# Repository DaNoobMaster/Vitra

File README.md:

# Vitra – AI Waste Classification System

Computer vision based trash can sorting system that runs on a raspberry-pi with a custom 3d printed model. Involves both a local model and 3 cloud based AI models for judgement. This creates a layer on top of all of the cloud models to merge results and increase accuracy. This project is intended to promote proper waste segregation and improve recycling opportunities. Using this in households can be a step in the right direction towards sustainability, a growing problem in our current society.

Waste is classified into 3 categories : 
- **Wet:** Food waste, banana peels, leftovers, and organic scraps.
- **Plastic:** Plastic bottles, containers, wrappers, and packaging.
- **Metal:** Metal cans, aluminium foil, and other metallic waste.

Prototype without PCB

BUILD INSTRUCTIONS-

-Corresponding Support arms are to be screwed into the male and female parts using M4 screws
-The male and female bin parts contain a dovetail slot in order to allow them to slide and lock with one another. Slide the male part into its female counterpart forming 1 large cylinderical bin.
-The Divider can be slided in between the cylinder.
-The Nema 17 Motor is to be mounted on the top disk
-The raspberry pi and servo are to be mounted on the arm
-the arm also contains dovetail joints to connect the camera holder to it while allowing it to print with ease.
-The raspberry pi camera is to be slid into the camera slot of the arm
-The arm is to be attached to a NEMA 17 coupler then attached to the nema 17

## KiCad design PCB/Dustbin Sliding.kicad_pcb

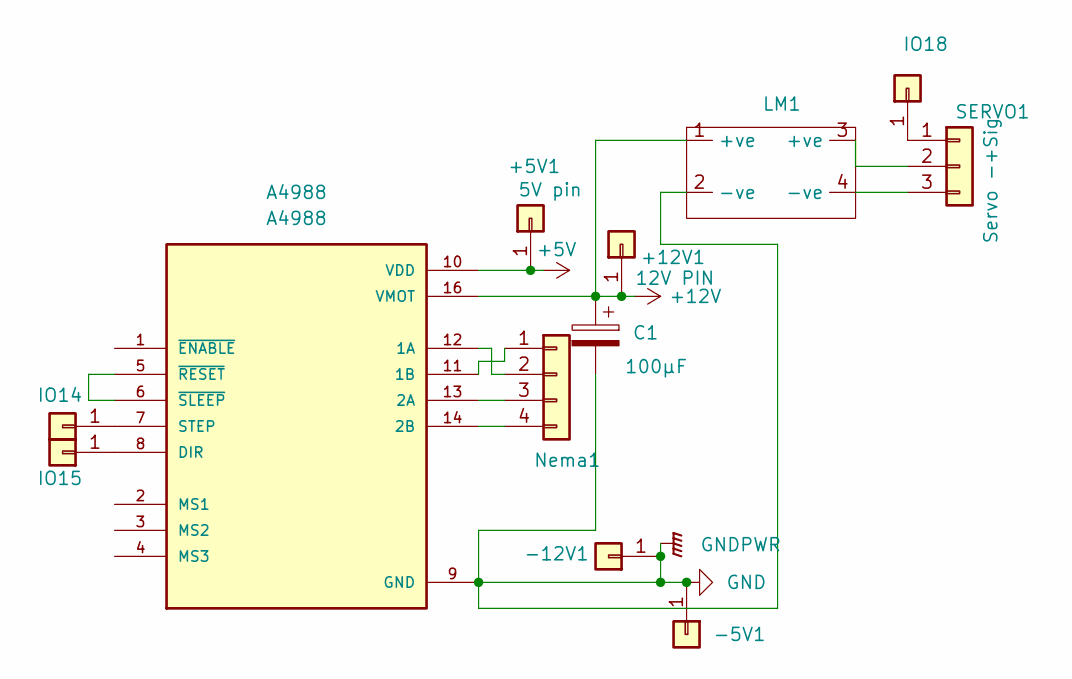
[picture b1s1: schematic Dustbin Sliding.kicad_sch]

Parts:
+5V1: 5V pin; PinHeader_1x01_P1.00mm_Vertical
+12V1: 12V PIN; PinHeader_1x01_P1.00mm_Vertical
-5V1: PI GND; PinHeader_1x01_P1.00mm_Vertical
-12V1: PWRGND; PinHeader_1x01_P1.00mm_Vertical
A4988: A4988; MODULE_A4988_STEPPER_MOTOR_DRIVER_CARRIER
C1: 100µF; CP_Radial_D10.0mm_P5.00mm
IO14: IO14; PinHeader_1x01_P1.00mm_Vertical
IO15: IO15; PinHeader_1x01_P1.00mm_Vertical
IO18: IO18
LM1: DC_DC_LM2596_small
Nema1: PinHeader_1x04_P1.00mm_Vertical
SERVO1: Servo -+Sig; PinHeader_1x03_P1.00mm_Vertical

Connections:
+5V: +5V1.1 (Pin_1_1), A4988.10 (VDD)
+12V: +12V1.1 (Pin_1_1), A4988.16 (VMOT), C1.1, LM1.1 (+ve)
GND: -5V1.1 (Pin_1_1), -12V1.1 (Pin_1_1), A4988.9 (GND), A4988.15 (GND), C1.2, LM1.2 (-ve)
unnamed: A4988.12 (1A), Nema1.2
unnamed: A4988.11 (1B), Nema1.1
unnamed: A4988.13 (2A), Nema1.3
unnamed: A4988.14 (2B), Nema1.4
unnamed: A4988.8 (DIR), IO15.1 (Pin_1_1)
unnamed: A4988.7 (STEP), IO14.1 (Pin_1_1)
unnamed: A4988.5 (~RESET), A4988.6 (~SLEEP)
unnamed: IO18.1, SERVO1.1
unnamed: LM1.3 (+ve), SERVO1.2
unnamed: LM1.4 (-ve), SERVO1.3

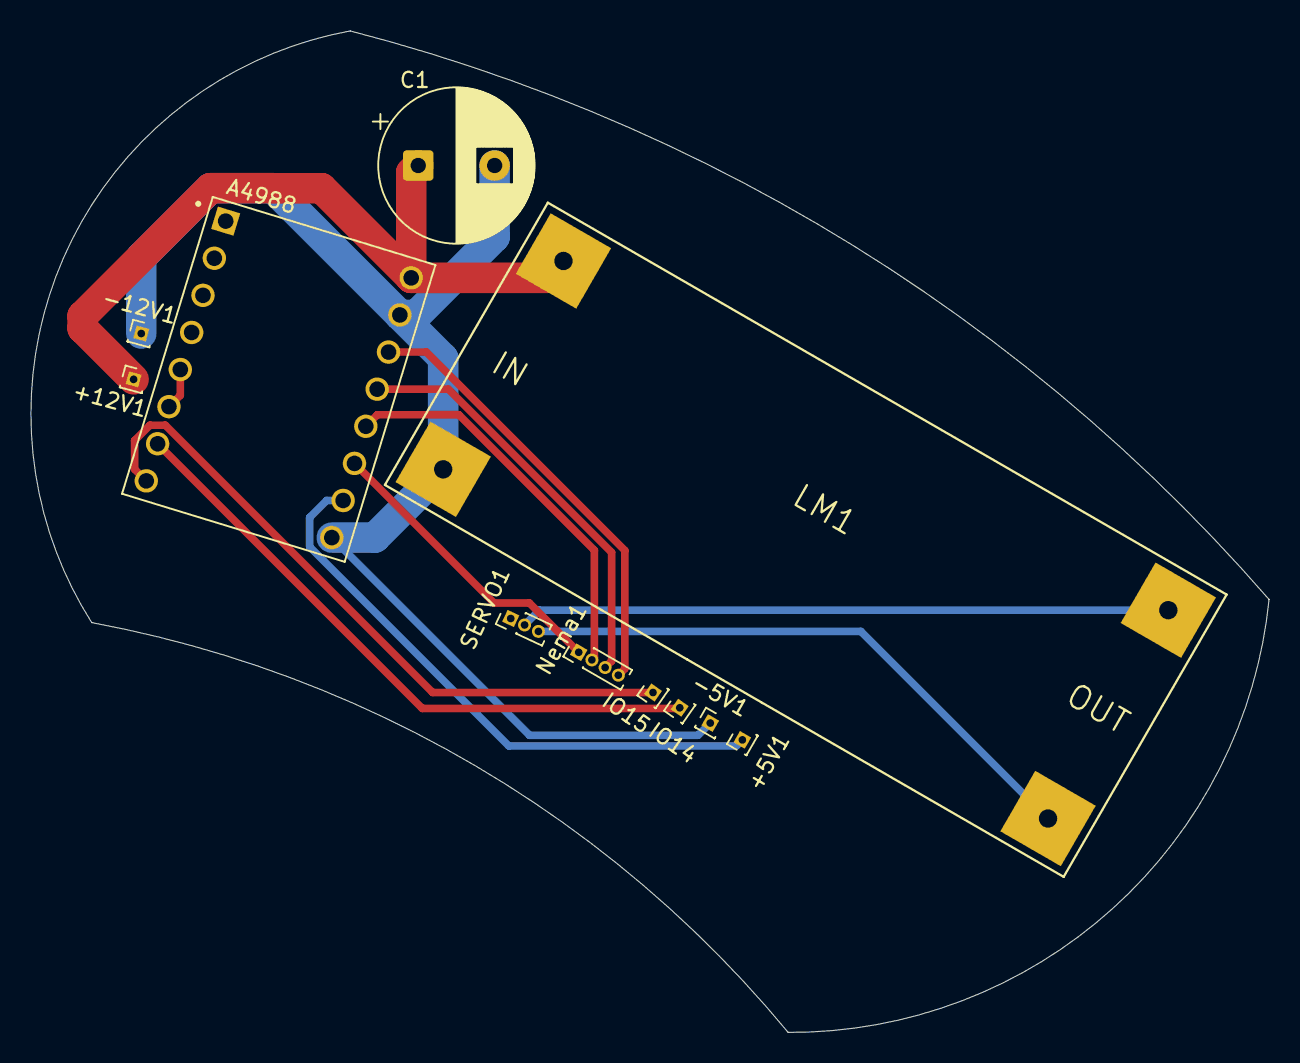
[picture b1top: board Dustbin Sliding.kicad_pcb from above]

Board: 2 copper layers, 81.1 x 65.6 mm, 11 parts (0 on the bottom side), 12 nets.

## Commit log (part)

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2026-05-29 Add initial README.md with script description
2026-05-29 Added images to readme file
2026-05-29 Fix typo in README.md
2026-05-29 Fix formatting in README.md
2026-05-29 Refactor recognition.py for better organization
    Refactor recognition.py to improve structure and clarity.
